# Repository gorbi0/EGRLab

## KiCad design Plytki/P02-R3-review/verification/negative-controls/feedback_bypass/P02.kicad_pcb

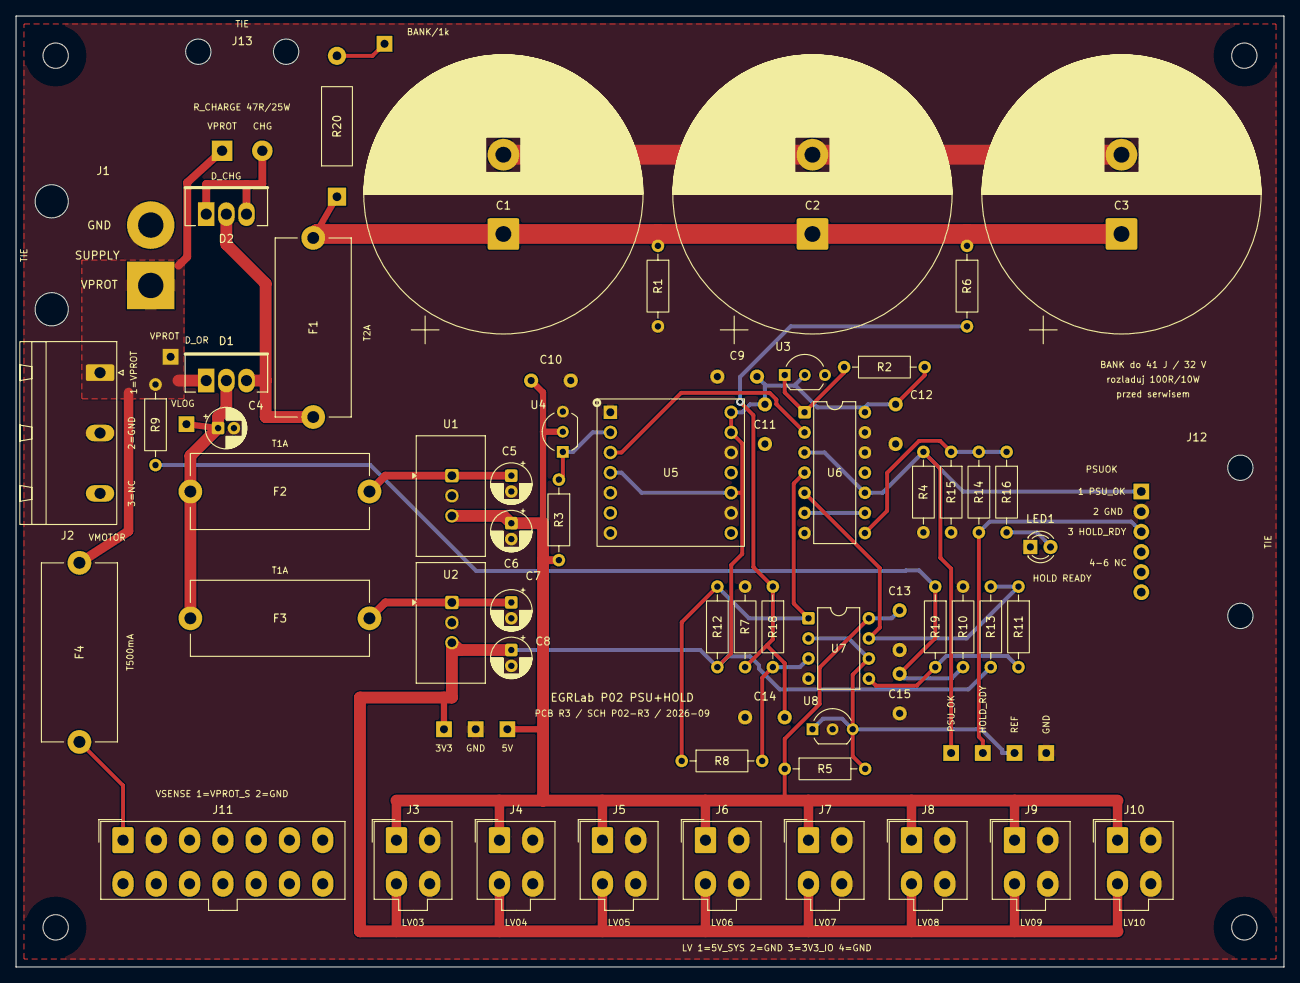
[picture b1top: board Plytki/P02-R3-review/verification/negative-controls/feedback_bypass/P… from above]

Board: 2 copper layers, 160.0 x 120.0 mm, 76 parts (0 on the bottom side), 27 nets.

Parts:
C1, C2, C3: 22000u; CP_Radial_D35.0mm_P10.00mm_SnapIn
C4, C6, C8: 22u; CP_Radial_D5.0mm_P2.00mm
C5, C7: 10u; CP_Radial_D5.0mm_P2.00mm
C9, C10, C11, C12, C13: 100nF; C_Vishay_K15_H5_P5
C14, C15: 10nF; C_Vishay_K15_H5_P5
D1, D2: STPS20100CT; TO220_3_P2.54_Drill1.4
F1: T2A; Fuseholder_Cylinder-5x20mm_Stelvio-Kontek_PTF78_Horizontal_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
F2, F3: T1A; Fuseholder_Cylinder-5x20mm_Stelvio-Kontek_PTF78_Horizontal_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
F4: T500mA; Fuseholder_Cylinder-5x20mm_Stelvio-Kontek_PTF78_Horizontal_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
H1, H2, H3, H4: M3 NPTH
J1: SUPPLY; Pigtail_PWR_2x2.5mm2
J2: VMOTOR; PhoenixContact_GMSTBA_2,5_3-G-7,62_1x03_P7.62mm_Horizontal
J3: LV03; Molex_Mini-Fit_Jr_5566-04A_2x02_P4.20mm_Vertical
J4: LV04; Molex_Mini-Fit_Jr_5566-04A_2x02_P4.20mm_Vertical
J5: LV05; Molex_Mini-Fit_Jr_5566-04A_2x02_P4.20mm_Vertical
J6: LV06; Molex_Mini-Fit_Jr_5566-04A_2x02_P4.20mm_Vertical
J7: LV07; Molex_Mini-Fit_Jr_5566-04A_2x02_P4.20mm_Vertical
J8: LV08; Molex_Mini-Fit_Jr_5566-04A_2x02_P4.20mm_Vertical
J9: LV09; Molex_Mini-Fit_Jr_5566-04A_2x02_P4.20mm_Vertical
J10: LV10; Molex_Mini-Fit_Jr_5566-04A_2x02_P4.20mm_Vertical
J11: VSENSE; Molex_Mini-Fit_Jr_5566-14A_2x07_P4.20mm_Vertical
J12: PSUOK; Pigtail_PSUOK_6x_P2.54
J13: R_CHARGE; Pigtail_RCHARGE_2xAWG20
LED1: GREEN 3mm; LED_D3.0mm
R1: 4K7; R_Axial_DIN0207_L6.3mm_D2.5mm_P10.16mm_Horizontal
R2, R3, R4, R7, R10, R12, R13, R15, R18, R19: 10K; R_Axial_DIN0207_L6.3mm_D2.5mm_P10.16mm_Horizontal
R5: 330R; R_Axial_DIN0207_L6.3mm_D2.5mm_P10.16mm_Horizontal
R6: 30K1; R_Axial_DIN0207_L6.3mm_D2.5mm_P10.16mm_Horizontal
R8, R11: 1M; R_Axial_DIN0207_L6.3mm_D2.5mm_P10.16mm_Horizontal
R9: 38K3; R_Axial_DIN0207_L6.3mm_D2.5mm_P10.16mm_Horizontal
R14: 1K; R_Axial_DIN0207_L6.3mm_D2.5mm_P10.16mm_Horizontal
R16: 470R; R_Axial_DIN0207_L6.3mm_D2.5mm_P10.16mm_Horizontal
R20: 1K; R_PR02_P17.78
TP1, TP2, TP3, TP4, TP5, TP6, TP7, TP8, TP9, TP10: TestPad_1
U1: TSR 2-2450; Converter_DCDC_TRACO_TSR2-xxxx_THT
U2: TSR 2-2433; Converter_DCDC_TRACO_TSR2-xxxx_THT
U3: MCP120-300DI/TO; TO-92_Inline_Wide
U4: MCP120-450DI/TO; TO-92_Inline_Wide
U5: 74LVC125A; Adapter_SO14_DIP14_W15.24_Kamami575068
U6: SN74HC08N; DIP-14_W7.62mm
U7: LM2903P; DIP-8_W7.62mm
U8: TL431BILP; TO-92_Inline_Wide

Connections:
3V3_IO: C8.1, C9.1, C11.1, C12.1, J3.3, J4.3, J5.3, J6.3, J7.3, J8.3, J9.3, J10.3, R2.2, R12.2, R13.2, TP5.1, U2.3, U3.2, U5.4, U5.10, U5.13, U5.14, U6.14
5V_SYS: C6.1, C10.1, C13.1, J3.1, J4.1, J5.1, J6.1, J7.1, J8.1, J9.1, J10.1, R3.2, R5.1, TP4.1, U1.3, U4.2, U7.8
/CHARGE_D: D2.1, D2.3, J13.2
/HOLD/P02_BANK_CMP: R18.2, U7.3
/HOLD/P02_BANK_DIV: C14.1, R6.2, R7.1, R8.2, R18.1
/HOLD/P02_REF25: R5.2, TP9.1, U7.2, U7.6, U8.1, U8.3
/HOLD/P02_VPROT_CMP: R11.2, R19.2, U7.5
/HOLD/P02_VPROT_DIV: C15.1, R9.2, R10.1, R19.1
/HOLD_FUSED: D1.3, D2.2, F1.1
/HOLD_TP: R20.2, TP3.1
/LV/P02_VIN_DC5: C5.1, F2.2, U1.1
/LV/P02_VIN_DC33: C7.1, F3.2, U2.1
/MON/HOLD_READY: J12.3, R14.2, TP8.1
/MON/P02_HOLD_QUAL: U6.6, U6.9
/MON/P02_HOLD_READY_INT: R14.1, R15.1, R16.1, U6.8
/MON/P02_LED_A: LED1.2, R16.2
/MON/P02_SUP3_N: R2.1, U3.1, U6.1
/MON/P02_SUP5_N: U5.3, U6.2
/MON/P02_SUP5_RAW: R3.1, U4.1, U5.2
/MON/PSU_OK: J12.1, R4.1, TP7.1, U6.3, U6.10
/VPROT_SENSE: F4.2, J11.1
GND: C1.2, C2.2, C3.2, C4.2, C5.2, C6.2, C7.2, C8.2, C9.2, C10.2, C11.2, C12.2, C13.2, C14.2, C15.2, J1.2, J2.2, J3.2, J3.4, J4.2, J4.4, J5.2, J5.4, J6.2, J6.4, J7.2, J7.4, J8.2, J8.4, J9.2, J9.4, J10.2, J10.4, J11.2, J12.2, LED1.1, R1.2, R4.2, R7.2, R10.2, R15.2, TP6.1, TP10.1, U1.2, U2.2, U3.3, U4.3, U5.1, U5.5, U5.7, U5.9, U5.12, U6.7, U6.12, U6.13, U7.4, U8.2
HOLD_STORE: C1.1, C2.1, C3.1, F1.2, R1.1, R6.1, R20.1
P02_BANK_OK: R8.1, R12.1, U6.4, U7.1
P02_VPROT_OK: R11.1, R13.1, U6.5, U7.7
VLOG_RES: C4.1, D1.2, F2.1, F3.1, TP2.1
VPROT: D1.1, F4.1, J1.1, J2.1, J13.1, R9.1, TP1.1

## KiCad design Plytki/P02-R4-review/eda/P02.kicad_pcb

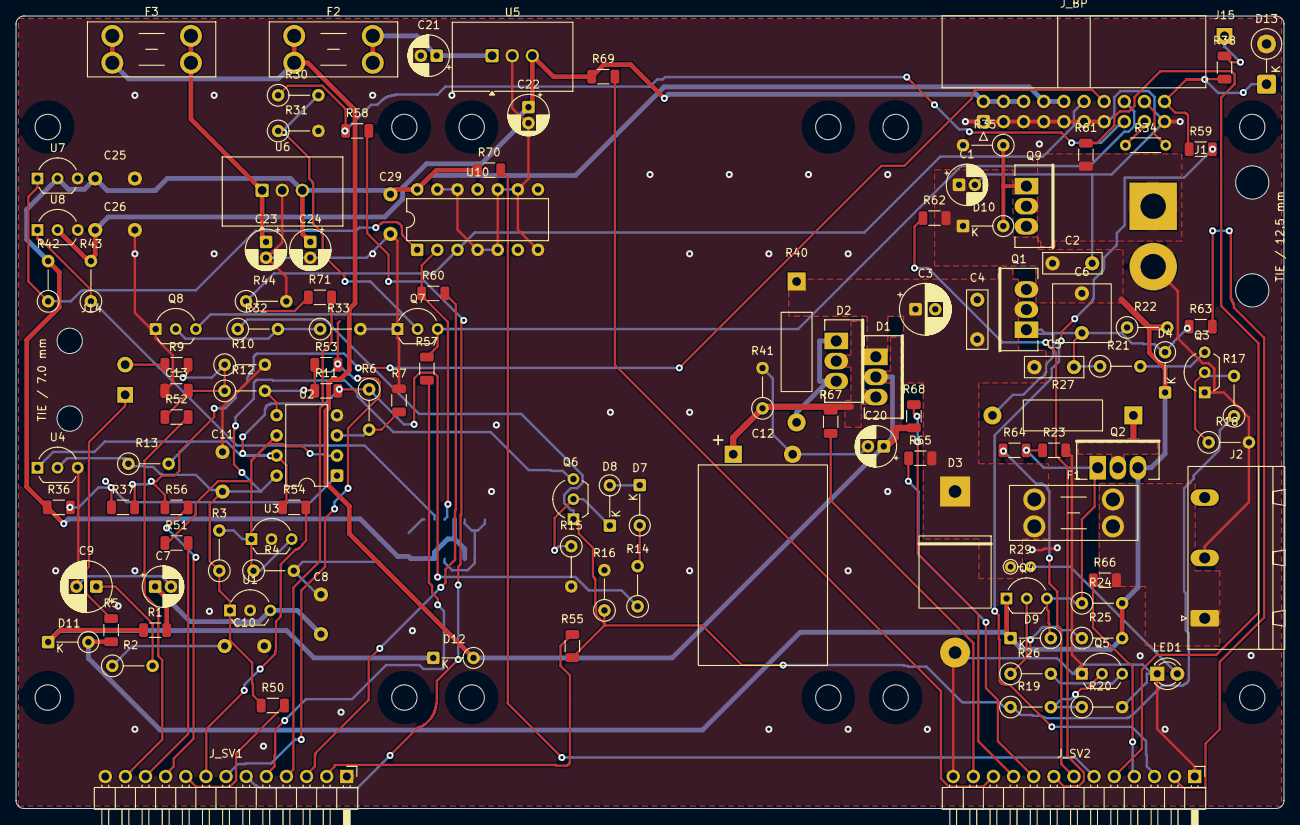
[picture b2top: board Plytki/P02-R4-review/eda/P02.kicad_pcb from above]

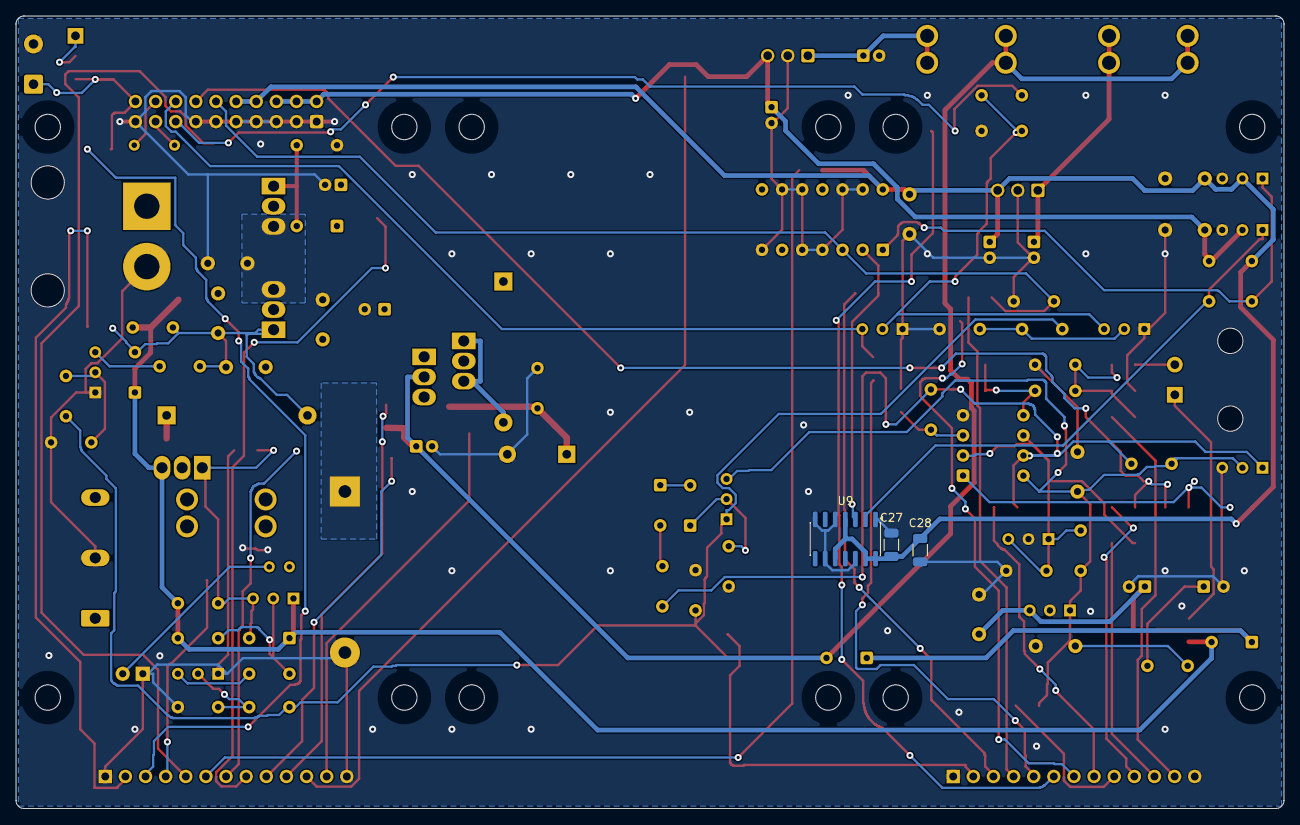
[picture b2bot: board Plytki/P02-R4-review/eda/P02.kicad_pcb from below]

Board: 2 copper layers, 160.0 x 100.0 mm, 139 parts (3 on the bottom side), 73 nets.

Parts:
C1, C21, C23: 10u; CP_Radial_D5.0mm_P2.00mm
C2, C4: 100nF; C_TDK_B32529_L7.3_W2.5_P5
C3, C9: 47u; CP_Radial_D6.3mm_P2.50mm
C5: 10nF; C_TDK_B32529_L7.3_W2.5_P5
C6: 1uF; C_WIMA_MKS2_1u100V_L7.2_W7.2_P5
C7, C20, C22, C24: 22u; CP_Radial_D5.0mm_P2.00mm
C8, C10, C11, C25, C26, C29: 100nF; C_Vishay_K15_H5_P5
C12: 2200u; CP_Radial_D16.0mm_L25mm_P7.50mm_Lying
C13: 10nF; C_1206_3216Metric
C27, C28: 100nF; C_1206_3216Metric
D1, D2: STPS20100CT; TO220_3_P2.54_Drill1.4
D3: 5KP24A; TVS_P600_P20.32
D4, D9, D10: BZX55C15; D_DO-35_SOD27_P5.08mm_Vertical_CathodeUp
D7, D8, D11, D12: 1N4148; D_DO-35_SOD27_P5.08mm_Vertical_CathodeUp
D13: P6KE24CA; D_DO-15_P5.08mm_Vertical_CathodeUp
F1: 5A; Fuseholder_Blade_Mini_Keystone_3568
F2, F3: 1A; Fuseholder_Blade_Mini_Keystone_3568
H1, H2, H3, H4, H5, H6, H7, H8, H9, H10, H11, H12: M3 NPTH
J1: BAT; Pigtail_PWR_2x2.5mm2
J2: VMOTOR; PhoenixContact_GMSTBA_2,5_3-G-7,62_1x03_P7.62mm_Horizontal
J14: PWR; Pigtail_PWR_SW_2xAWG22_T7
J15: VBAT_IN; Pigtail_VBAT_1xAWG22
J_BP: J_BP; IDC-Header_2x10_P2.54mm_Horizontal
J_SV1: J_SV1; PinHeader_1x13_P2.54mm_Horizontal
J_SV2: J_SV2; PinHeader_1x13_P2.54mm_Horizontal
LED1: GREEN 3mm; LED_D3.0mm
Q1, Q2, Q9: SUP53P06-20; TO220_3_P2.54_Drill1.4
Q3, Q5, Q6, Q7, Q8: 2N5551G; TO-92_Inline_Wide
Q4: 2N5401YBU; TO-92_Inline_Wide
R1: 47R; R_1206_3216Metric
R2: 1R; R_Axial_DIN0207_L6.3mm_D2.5mm_P5.08mm_Vertical
R3: 820R; R_Axial_DIN0207_L6.3mm_D2.5mm_P5.08mm_Vertical
R4, R10, R12, R16, R26, R30, R32, R41, R42, R43, R44: 10K; R_Axial_DIN0207_L6.3mm_D2.5mm_P5.08mm_Vertical
R5, R37, R50, R54, R55, R56, R57, R58, R60, R69, R70, R71: 1K; R_1206_3216Metric
R6, R15, R21, R24, R31, R35: 100K; R_Axial_DIN0207_L6.3mm_D2.5mm_P5.08mm_Vertical
R7: 150K; R_1206_3216Metric
R9: 41K2; R_1206_3216Metric
R11: 464K; R_1206_3216Metric
R13: 2K2; R_Axial_DIN0207_L6.3mm_D2.5mm_P5.08mm_Vertical
R14, R17, R19: 4K7; R_Axial_DIN0207_L6.3mm_D2.5mm_P5.08mm_Vertical
R18, R20, R25, R33: 47K; R_Axial_DIN0207_L6.3mm_D2.5mm_P5.08mm_Vertical
R22: 470K; R_Axial_DIN0207_L6.3mm_D2.5mm_P5.08mm_Vertical
R23: 22K; R_1206_3216Metric
R27: 10R; R_PR02_P17.78
R29: 6K8; R_Axial_DIN0204_L3.6mm_D1.6mm_P2.54mm_Vertical
R34: 0R; R_Axial_DIN0204_L3.6mm_D1.6mm_P5.08mm_Horizontal
R36, R38, R51, R52, R53, R59, R63, R64: 10K; R_1206_3216Metric
R40: 22R; R_PR02_P17.78
R61, R62, R65, R66, R67, R68: 4K7; R_1206_3216Metric
U1: LM2936Z-5.0; TO-92_Inline_Wide
U2: LM2903P; DIP-8_W7.62mm
U3: TL431BILP; TO-92_Inline_Wide
U4, U8: MCP120-450DI/TO; TO-92_Inline_Wide
U5: TSR 2-2450; Converter_DCDC_TRACO_TSR2-xxxx_THT
U6: TSR 2-2433; Converter_DCDC_TRACO_TSR2-xxxx_THT
U7: MCP120-300DI/TO; TO-92_Inline_Wide
U9: 74LVC125A; SOIC-14_3.9x8.7mm_P1.27mm
U10: SN74HC08N; DIP-14_W7.62mm

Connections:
3V3_IO: C24.1, C25.1, C27.1, C28.1, C29.1, J_BP.8, J_BP.10, R36.1, R42.2, R70.1, U6.3, U7.2, U9.4, U9.10, U9.13, U9.14, U10.14
5V_SYS: C22.1, C26.1, J_BP.2, J_BP.4, J_BP.6, R43.2, R69.1, U5.3, U8.2
/LV/P02_VIN_DC5: C21.1, F2.2, U5.1
/LV/P02_VIN_DC33: C23.1, F3.2, U6.1
/MON/P02_SUP3_N: R42.1, U7.1, U10.1
/MON/P02_SUP5_RAW: R43.1, U8.1, U9.2
/MON/VBAT_CAR: J15.1, R38.1
/P02_CH_A: D2.1, D2.3, R40.2
/P02_OFF_D: Q2.2, R27.1
/P02_ON_B: Q3.2, R17.2, R18.1
/P02_ON_COL: Q3.3, R21.2
/P02_REL_B: Q5.2, R19.2, R20.1
/P02_REL_COL: Q5.3, R26.2
/P02_REL_PB: Q4.2, R25.1, R26.1
/P02_REV_G: D10.2, Q9.1, R35.1
/SERW/P02_SV_3V3_IO: J_SV2.6, R70.2
/SERW/P02_SV_5V_SYS: J_SV2.11, R69.2
/SERW/P02_SV_AUX5: J_SV1.9, R50.2
/SERW/P02_SV_BAT_IN: J_SV2.5, R61.2
/SERW/P02_SV_ENABLE: J_SV1.2, R55.2
/SERW/P02_SV_GATE: J_SV2.2, R63.2
/SERW/P02_SV_HOLD_C: J_SV2.12, R67.2
/SERW/P02_SV_OFF_G: J_SV2.7, R64.2
/SERW/P02_SV_OK: J_SV1.8, R54.2
/SERW/P02_SV_P04_3V3: J_SV1.6, R58.2
/SERW/P02_SV_PFAIL_N: J_SV1.10, R56.2
/SERW/P02_SV_PSU_OK: J_SV1.4, R71.2
/SERW/P02_SV_REF: J_SV1.11, R51.2
/SERW/P02_SV_SAFE_N: J_SV1.5, R57.2
/SERW/P02_SV_SUP5_N: J_SV1.3, R60.2
/SERW/P02_SV_SW_COM: J_SV2.8, R62.2
/SERW/P02_SV_UV_CMP: J_SV1.7, R53.2
/SERW/P02_SV_UV_DIV: J_SV1.12, R52.2
/SERW/P02_SV_VBAT_SENSE: J_SV2.3, R59.2
/SERW/P02_SV_VLOG: J_SV2.10, R68.2
/SERW/P02_SV_VMOTOR: J_SV2.4, R66.2
/SERW/P02_SV_VSW: J_SV2.9, R65.2
/STER/P02_AUX_IN: C7.1, C8.1, R1.2, U1.3
/STER/P02_BUF_BASE: D8.1, Q6.2, R15.1
/STER/P02_BUF_D1: D7.2, R14.2
/STER/P02_BUF_D2: D7.1, D8.2
/STER/P02_C_AUX_TOP: C9.1, R2.2
/STER/P02_FAULT_B: Q7.2, Q8.3, R30.2, R31.1
/STER/P02_FAULT_REL_B: Q8.2, R32.2, R33.1
/STER/P02_LED_A: LED1.2, R29.2
/STER/P02_PFAIL_OC: R36.2, R37.1, U2.1
/STER/P02_PF_IN: R6.2, R7.1, U2.3
/STER/P02_PWR_A: J14.1, R5.2
/STER/P02_PWR_B: J14.2, R9.1
/STER/P02_V_CTRL: D11.1, D12.1, R1.1
GND: C1.2, C2.2, C3.2, C4.2, C7.2, C8.2, C9.2, C10.2, C11.2, C12.2, C13.2, C20.2, C21.2, C22.2, C23.2, C24.2, C25.2, C26.2, C27.2, C28.2, C29.2, D3.2, D13.2, J1.2, J2.2, J_BP.1, J_BP.3, J_BP.5, J_BP.7, J_BP.9, J_BP.11, J_BP.13, J_BP.19, J_SV1.1, J_SV1.13, J_SV2.1, J_SV2.13, LED1.1, Q3.1, Q5.1, Q7.1, Q8.1, R4.2, R7.2, R10.2, R15.2, R16.2, R18.2, R20.2, R23.2, R31.2, R33.2, R35.2, R41.2, R44.2, U1.2, U2.4, U3.2, U4.3, U5.2, U6.2, U7.3, U8.3, U9.1, U9.5, U9.7, U9.9, U9.12, U10.4, U10.5, U10.7, U10.9, U10.10, U10.12, U10.13
P02_AUX5: C10.1, C11.1, Q6.3, R2.1, R3.1, R13.1, R50.1, U1.1, U2.8, U4.2
P02_BAT_IN: J1.1, Q9.2, R61.1
P02_ENABLE: Q6.1, R16.1, R17.1, R19.1, R32.1, R55.1
P02_GATE: C5.1, C6.1, D4.2, Q1.1, R21.1, R22.1, R27.2, R63.1
P02_HOLD_C: C12.1, D1.3, D2.2, R41.1, R67.1
P02_OFF_G: D9.2, Q2.1, Q4.3, R23.1, R24.1, R64.1
P02_OK: R6.1, R11.1, R13.2, R14.1, R54.1, U2.7, U4.1
P02_REF: R3.2, R4.1, R51.1, U2.2, U2.6, U3.1, U3.3
P02_SUP5_N: R60.1, U9.3, U10.2
P02_SW_COM: C1.1, C2.1, C6.2, D4.1, D9.1, D10.1, D11.2, Q1.3, Q2.3, Q4.1, Q9.3, R5.1, R22.2, R24.2, R25.2, R62.1
P02_UV_CMP: R11.2, R12.2, R53.1, U2.5
P02_UV_DIV: C13.1, R9.2, R10.1, R12.1, R52.1
P02_VLOG: C20.1, D1.2, D12.2, F2.1, F3.1, R68.1
P02_VSW: C3.1, C4.1, C5.2, D1.1, D3.1, F1.1, Q1.2, R29.1, R40.1, R65.1
P04_3V3: J_BP.15, R30.1, R58.1
PFAIL_N: J_BP.14, R37.2, R56.1
PG_LINK: J_BP.18, R34.2
PG_SEND: J_BP.17, R34.1
PSU_OK: J_BP.12, R44.1, R71.1, U10.3
SAFE_N: J_BP.16, Q7.3, R57.1
VBAT_SENSE: D13.1, J_BP.20, R38.2, R59.1
VMOTOR: F1.2, J2.1, R66.1
